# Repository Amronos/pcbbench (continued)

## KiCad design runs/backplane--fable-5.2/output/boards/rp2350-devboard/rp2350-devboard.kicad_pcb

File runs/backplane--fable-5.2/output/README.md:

# RP2350 Wi-Fi/BLE dev board (rev A)

A 76.2 x 22.86 mm, 4-layer RP2350A development board with Wi-Fi/BLE, LiPo charging with power path,
microSD, Qwiic and an addressable RGB LED. All 71 components sit on the top side so PCBWay can build it
with a single-sided SMT pass.

**Status: designed, not built.** ERC is clean; DRC is clean (0 errors, 0 unconnected, schematic parity OK,
one harmless "dangling via" warning). Nothing here has been verified on hardware — read
"What a reviewer should check" before ordering.

## Where things are

| Path | What |
|---|---|
| `boards/rp2350-devboard/` | KiCad project: `.kicad_pro`, `.kicad_sch`, `.kicad_pcb`, project symbol lib, custom DRC rule |
| `fab/rp2350-devboard-gerbers.zip` | Gerbers (RS-274X, 4 copper layers) + Excellon drill files — upload this to PCBWay |
| `fab/gerbers/` | The same files unzipped |
| `fab/assembly/rp2350-devboard-bom.csv` | BOM in PCBWay's column layout (36 lines, 71 parts, all SMD) |
| `fab/assembly/rp2350-devboard-centroid.csv` | Pick-and-place file (origin = bottom-left board corner, mm) |
| `fab/assembly/rp2350-devboard-assembly-top.pdf` | Assembly drawing with reference designators and notes |
| `fab/docs/` | Schematic PDF, fab drawing, IPC-D-356 netlist, STEP model, renders |
| `tools/` | Generator scripts. `tools/design.py` is the single source for parts, nets and placement |

The files were made with Backplane KiCad 10.99 (newer file format than stock KiCad 10.0).

## PCBWay order settings

- 4 layers, 76.2 x 22.86 mm, 1.6 mm FR-4, 1 oz outer / 0.5 oz inner is fine
- Min track/space **0.15 / 0.10 mm** (the 0.10 mm spacing occurs only where VREG_LX passes between two 0402 pads; everything else is ≥ 0.15 mm), min hole 0.3 mm, via 0.6 / 0.3 mm
- Finish: ENIG (0.4 mm pitch QFN-60), any solder-mask colour, vias tented
- Assembly: top side only, turnkey. Stencil top only
- **Not populated on purpose:** the two 1x12 2.54 mm header rows (J5, J6) and the three bottom-side SWD test pads (TP1–TP3). They are bare holes/pads and are excluded from BOM and centroid
- **L1 is polarised**: the dot on the Abracon inductor goes to pad 1 (+1V1 net, the pad towards the bottom board edge). This is in the BOM notes and on the assembly drawing

## What is on the board

| Function | Part | Notes |
|---|---|---|
| MCU | RP2350A (QFN-60, A4 stepping) | on-chip 1.1 V SMPS with the Abracon AOTA-B201610S3R3-101-T inductor, 12 MHz ABM8-272-T3 crystal |
| Flash | W25Q128JVPIQ, 16 MB | QSPI CS0 |
| PSRAM | APS6404L-3SQR-ZR, 8 MB | QSPI CS1 on GPIO0, 10 k pull-up |
| USB | USB-C (HRO TYPE-C-31-M-12) | 5.1 k CC resistors, USBLC6-2SC6 ESD, 27 Ω series resistors |
| Charger | BQ24074 | power path, ~300 mA charge, 500 mA USB input limit, orange CHG LED |
| 3.3 V | TLV75733P 1 A LDO | fed from the charger's system output; EN on a header pin |
| Battery monitor | 200 k / 200 k divider + 100 nF | VBAT/2 on GPIO29 (ADC3) |
| Wi-Fi / BLE | Raspberry Pi Radio Module 2 (CYW43439) | wired like Pico 2 W, user LED on the module's GPIO0 |
| microSD | Molex 104031-0811 | 4-bit SDIO or SPI0, card-detect on GPIO1 |
| Qwiic / STEMMA QT | JST SM04B-SRSS-TB | I2C0 on GPIO24/25 with 2.2 k pull-ups |
| RGB LED | WS2812B-2020 (V6) | GPIO23, powered from 3.3 V |
| Buttons | 2 x Omron B3U-1000P | BOOT (QSPI_SS through 1 k) and RST (RUN) |

### Pin map

| GPIO | Use | GPIO | Use |
|---|---|---|---|
| 0 | PSRAM CS (XIP_CS1) | 16 | RM2 WL_ON (also BT_ON) |
| 1 | SD card detect (low = card in) | 17 | RM2 CS |
| 2 | SD CLK (SPI0 SCK) | 18 | RM2 data (DIN direct, DOUT via 470 Ω, IRQ via 10 k) |
| 3 | SD CMD (SPI0 TX) | 19 | RM2 clock |
| 4 | SD D0 (SPI0 RX) | 20–22 | header |
| 5, 6 | SD D1, D2 | 23 | RGB LED data |
| 7 | SD D3 / CS | 24, 25 | SDA, SCL (header + Qwiic) |
| 8–15 | header | 26–28 | header (ADC0–2) |
| | | 29 | battery voltage / 2 (ADC3) |

Headers (0.8" row spacing, breadboard-friendly, pin 1 nearest the USB end):

- Top row: VBUS, VBAT, EN, GND, GP28, GP27, GP26, SCL (GP25), SDA (GP24), GP22, GP21, GP20
- Bottom row: 3V3, GND, VSYS, GND, GP8, GP9, GP10, GP11, GP12, GP13, GP14, GP15

Pin names are printed on the bottom silkscreen. SWCLK, SWDIO and GND are test pads on the bottom.

For the Pico SDK, build for a Pico 2 W-style board with `CYW43_PIN_WL_REG_ON=16`, `CYW43_PIN_WL_CS=17`,
`CYW43_PIN_WL_DATA_OUT/IN/HOST_WAKE=18`, `CYW43_PIN_WL_CLOCK=19`.

## Key decisions

- **RP2350A, not B.** 30 GPIO is enough: 14 are used on the board and 16 go to the headers.
- **Raspberry Pi RM2 for the radio** rather than an ESP32 co-processor. It works with the stock Pico SDK / MicroPython CYW43 driver, carries its own antenna and modular certification, and needs only four GPIOs. The antenna end sits at the board edge with a 5 mm copper-free strip on all layers.
- **BQ24074 + LDO.** A true power path lets the board run from USB with no battery or a flat one. I chose an LDO over a buck-boost to keep the layout simple; the cost is that 3.3 V sags once the cell drops below about 3.5 V (the RM2 wants ≥ 3.0 V, ≥ 3.2 V for full RF performance).
- **Charge current ~300 mA** (R7 = 3.0 k; I = 890 / R7). Suits cells of 300 mAh and up; change R7 for other cells.
- **Regulator layout copies the Raspberry Pi reference**: VREG_LX runs between the pads of the input and output capacitors to the inductor, with one shared capacitor for pins 53/54. That is where the 0.10 mm spacing comes from (a custom DRC rule allows it for that net only).
- **All parts on top.** This made the board long (76 mm). Putting the microSD socket on the back would save about 14 mm at the price of double-sided assembly.
- **How the files were made.** Schematic and board are generated from `tools/design.py`. The RP2350 fan-out, regulator, QSPI, SD bus and other critical routes are explicit coordinates in that file; the remaining ~60 connections were finished by a small grid router (`tools/maze.py`) and checked with KiCad's DRC. The routing is electrically clean but not hand-polished.

## What a reviewer should check

1. **Battery polarity.** J2 pin 2 (marked `+`, the pad nearer the bottom edge) is positive. I could not confirm this matches the common Adafruit/SparkFun JST-PH wiring. Check your cell before plugging in — there is no reverse-polarity protection.
2. **microSD card-detect pins.** I wired socket pad 9 to GPIO1 and pad 10 to GND, assuming the switch sits between those two pads. If Molex's drawing says otherwise, card detect will read wrong; the card itself still works.
3. **RM2 footprint** is KiCad's library footprint `RF_Module:RMC20452T`; I checked its pad positions against the RM2 datasheet drawing, not against a physical module.
4. **Three signals use short tracks on In2** (the 3.3 V plane): QSPI SD1 and SD2 to the PSRAM, PSRAM CS, and RUN to the reset button. They were the only way to cross the SD bus and radio lines with single-sided assembly. They cut narrow slots in the plane; the GND plane on In1 is unbroken.
5. **Decoupling is a compromise.** Most mid-side RP2350 supply pins drop to the planes through vias inside the pad ring, with their 100 nF capacitors 3–6 mm away. Raspberry Pi's own minimal design makes a similar trade, but this is the first thing I would probe on a prototype (1.1 V ripple under Wi-Fi load).
6. **Things left out to keep the layout routable:**
   - no external pull-ups on the SD lines (use the RP2350's internal ones);
   - no external pull-up on RUN (internal only) and RUN is not on a header pin;
   - the RM2's GPIO2 is not wired to VBUS sense as on a Pico W;
   - no fiducials or mounting holes.
7. **Battery sense leakage.** The divider draws about 10 µA from the cell all the time, and GPIO29 is not fail-safe: with 3.3 V switched off through EN a few µA flow into the pin.
8. **Power track widths** are 0.25–0.4 mm for VBUS/VBAT/VSYS. That is adequate for the 500 mA input limit but not generous.
9. **BOM part numbers.** ICs, connectors, LEDs and switches were checked against LCSC stock on 2026-11-09 (the RM2 had only 51 pieces there; PCBWay may source it elsewhere). The Yageo/Samsung passive part numbers were written from the manufacturers' naming scheme and not looked up — any equivalent 0402/0603 part of the same value and rating is fine.
10. The USB pair is routed for full-speed only (no impedance control), which is all the RP2350 supports.

## Regenerating

```
tools/build_all.sh            # schematic, netlist check, pours, DRC, fab outputs (keeps the routing)
tools/build_all.sh --reroute  # also throws the routing away and routes again (about 2 minutes)
```

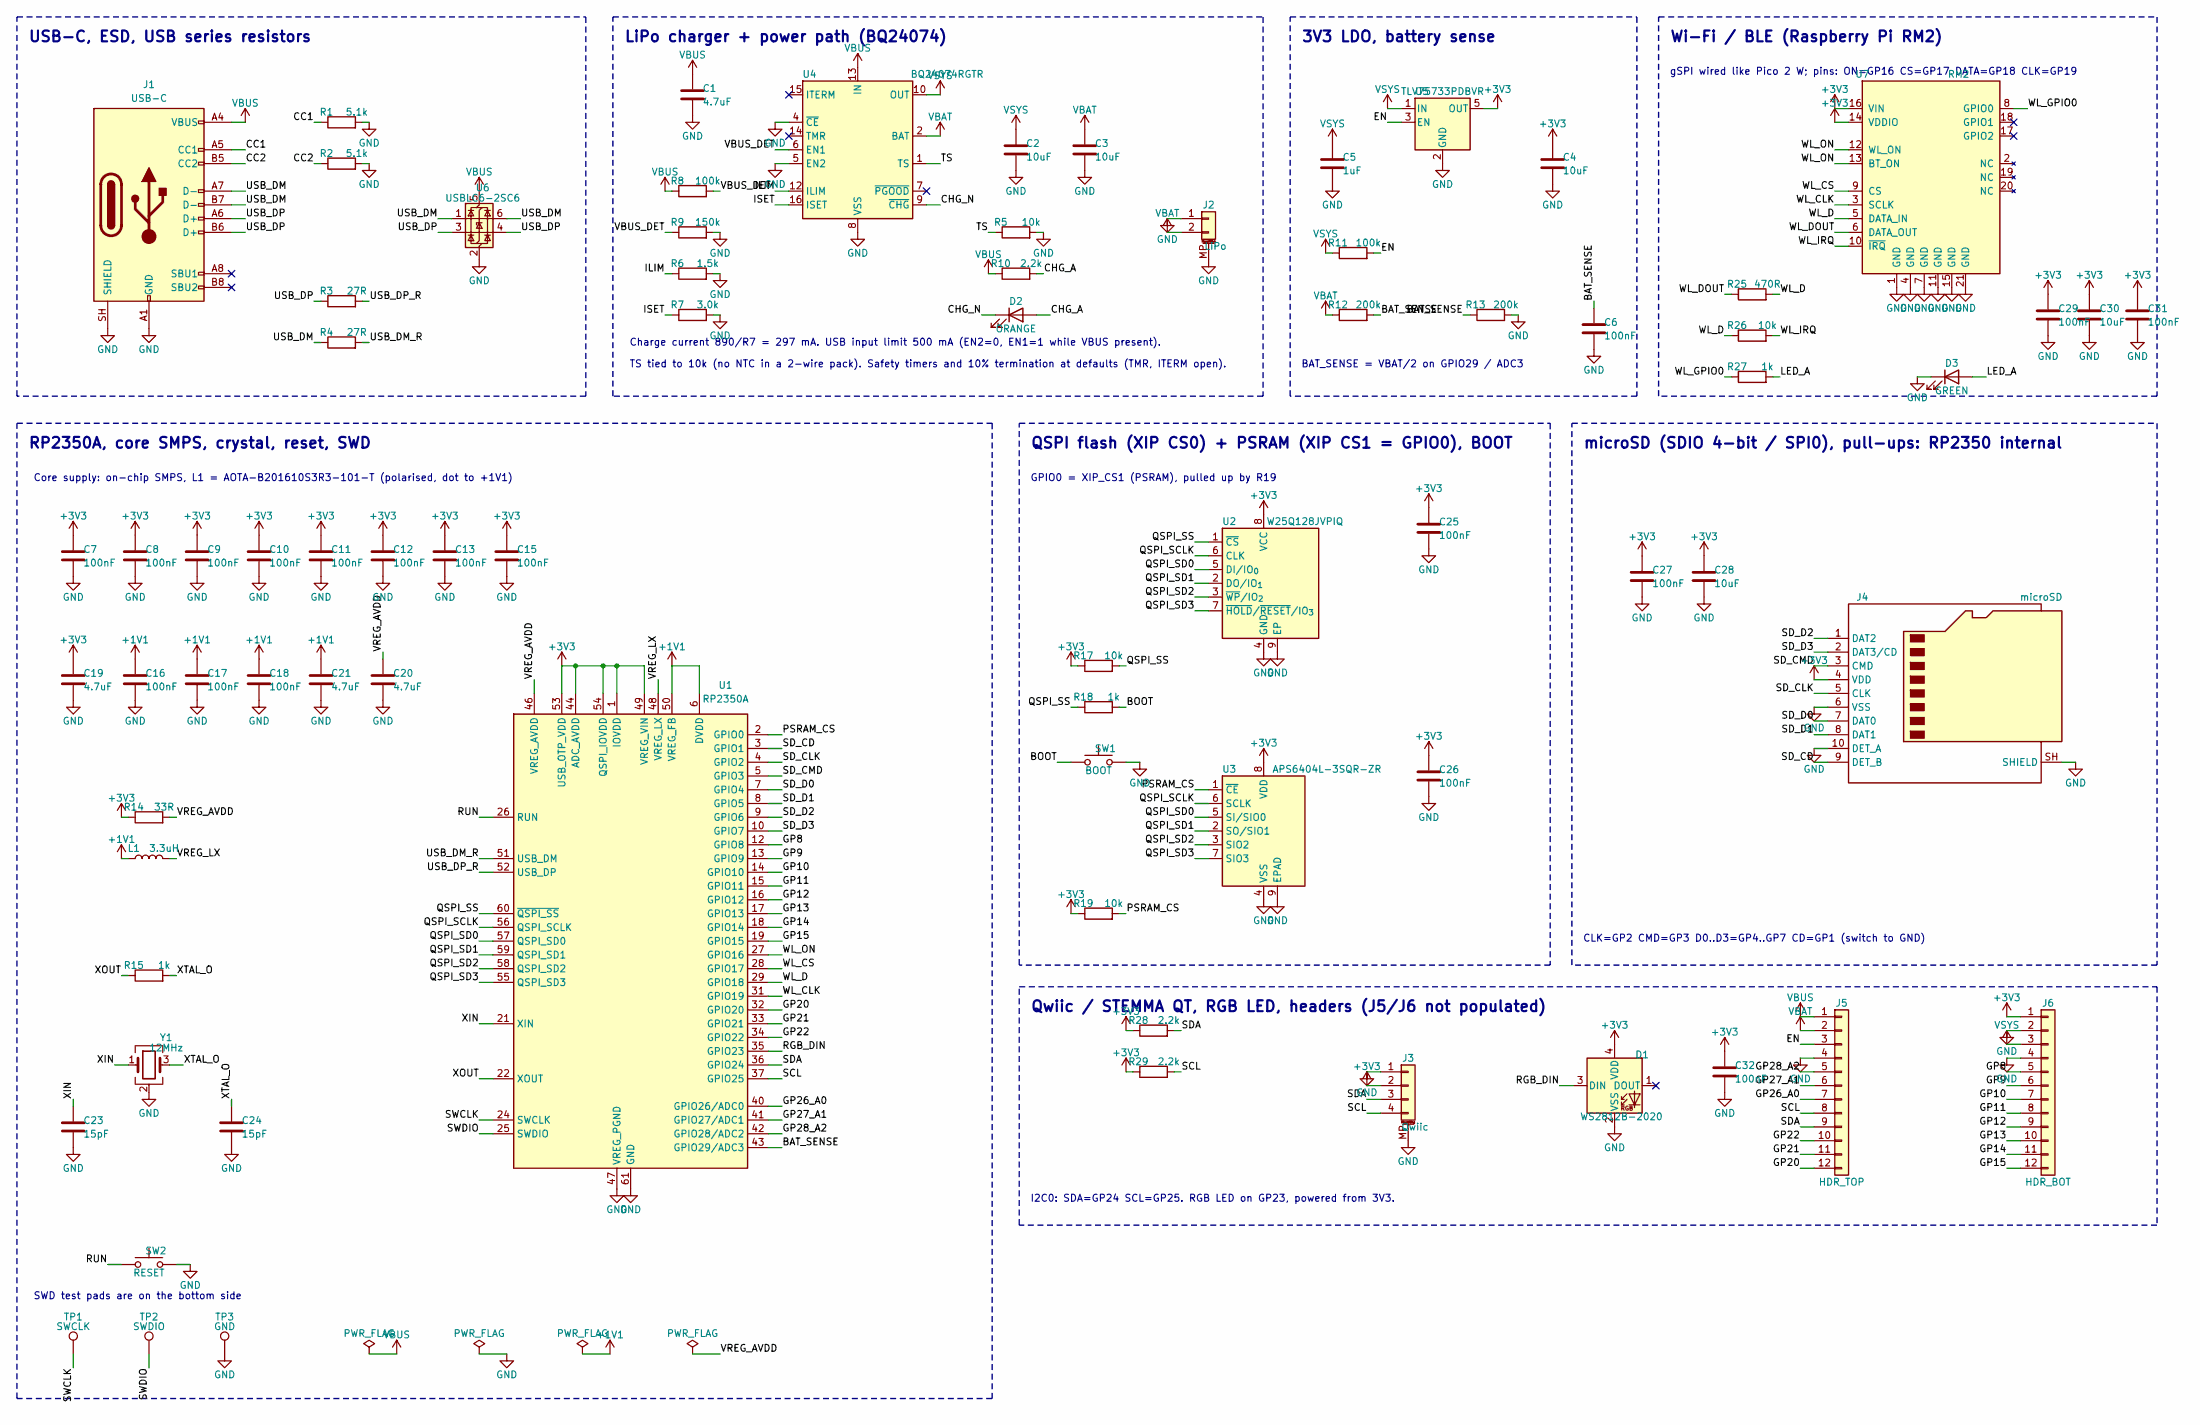
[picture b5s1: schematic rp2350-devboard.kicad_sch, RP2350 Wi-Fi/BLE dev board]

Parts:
C1: 4.7uF; C_0603_1608Metric; MPN CL10A475KA8NQNC
C2, C3, C4, C28, C30: 10uF; C_0603_1608Metric; MPN CL10A106MA8NRNC
C5: 1uF; C_0402_1005Metric; MPN CL05A105KA5NQNC
C6, C7, C8, C9, C10, C11, C12, C13, C15, C16, C17, C18, C25, C26, C27, C29, C31, C32: 100nF; C_0402_1005Metric; MPN CL05B104KO5NNNC
C19, C20, C21: 4.7uF; C_0402_1005Metric; MPN CL05A475MP5NRNC
C23, C24: 15pF; C_0402_1005Metric; MPN CL05C150JB5NNNC
D1: WS2812B-2020; LED_WS2812B-2020_PLCC4_2.0x2.0mm; MPN WS2812B-2020; LCSC C52917434
D2: ORANGE; LED_0603_1608Metric; MPN XL-1608UOC-06; LCSC C965800
D3: GREEN; LED_0603_1608Metric; MPN XL-1608SYGC-06; LCSC C965805
J1: USB-C; USB_C_Receptacle_HRO_TYPE-C-31-M-12; MPN TYPE-C-31-M-12; LCSC C165948
J2: LiPo; JST_PH_S2B-PH-SM4-TB_1x02-1MP_P2.00mm_Horizontal; MPN S2B-PH-SM4-TB(LF)(SN); LCSC C295747
J3: Qwiic; JST_SH_SM04B-SRSS-TB_1x04-1MP_P1.00mm_Horizontal; MPN SM04B-SRSS-TB(LF)(SN); LCSC C160404
J4: microSD; microSD_HC_Molex_104031-0811; MPN 104031-0811; LCSC C585350
J5: HDR_TOP; PinHeader_1x12_P2.54mm_Vertical
J6: HDR_BOT; PinHeader_1x12_P2.54mm_Vertical
L1: 3.3uH; L_Murata_DFE201610P; MPN AOTA-B201610S3R3-101-T; LCSC C42411119
R1, R2: 5.1k; R_0402_1005Metric; MPN RC0402FR-075K1L
R3, R4: 27R; R_0402_1005Metric; MPN RC0402FR-0727RL
R5, R17, R19, R26: 10k; R_0402_1005Metric; MPN RC0402FR-0710KL
R6: 1.5k; R_0402_1005Metric; MPN RC0402FR-071K5L
R7: 3.0k; R_0402_1005Metric; MPN RC0402FR-073KL
R8, R11: 100k; R_0402_1005Metric; MPN RC0402FR-07100KL
R9: 150k; R_0402_1005Metric; MPN RC0402FR-07150KL
R10, R28, R29: 2.2k; R_0402_1005Metric; MPN RC0402FR-072K2L
R12, R13: 200k; R_0402_1005Metric; MPN RC0402FR-07200KL
R14: 33R; R_0402_1005Metric; MPN RC0402FR-0733RL
R15, R18, R27: 1k; R_0402_1005Metric; MPN RC0402FR-071KL
R25: 470R; R_0402_1005Metric; MPN RC0402FR-07470RL
SW1: BOOT; SW_SPST_B3U-1000P; MPN B3U-1000P; LCSC C231329
SW2: RESET; SW_SPST_B3U-1000P; MPN B3U-1000P; LCSC C231329
TP1: SWCLK; TestPoint_Pad_D1.0mm
TP2: SWDIO; TestPoint_Pad_D1.0mm
TP3: GND; TestPoint_Pad_D1.5mm
U1: RP2350A; QFN-60-1EP_7x7mm_P0.4mm_EP3.4x3.4mm; MPN RP2350A0A4; LCSC C42411118
U2: W25Q128JVPIQ; WSON-8-1EP_6x5mm_P1.27mm_EP3.4x4.3mm; MPN W25Q128JVPIQ; LCSC C190862
U3: APS6404L-3SQR-ZR; Winbond_USON-8-1EP_3x2mm_P0.5mm_EP0.2x1.6mm; MPN APS6404L-3SQR-ZR; LCSC C3040877
U4: BQ24074RGTR; VQFN-16-1EP_3x3mm_P0.5mm_EP1.6x1.6mm; MPN BQ24074RGTR; LCSC C54313
U5: TLV75733PDBVR; SOT-23-5; MPN TLV75733PDBVR; LCSC C485517
U6: USBLC6-2SC6; SOT-23-6; MPN USBLC6-2SC6; LCSC C7519
U7: RM2; RMC20452T; MPN RMC20452T; LCSC C49451547
Y1: 12MHz; Crystal_SMD_3225-4Pin_3.2x2.5mm; MPN ABM8-272-T3; LCSC C20625731

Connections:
+1V1: C16.1, C17.1, C18.1, C21.1, L1.1, U1.6 (DVDD), U1.23 (DVDD), U1.39 (DVDD), U1.50 (VREG_FB)
+3V3: C4.1, C7.1, C8.1, C9.1, C10.1, C11.1, C12.1, C13.1, C15.1, C19.1, C25.1, C26.1, C27.1, C28.1, C29.1, C30.1, C31.1, C32.1, D1.4 (VDD), J3.2, J4.4 (VDD), J6.1, R14.1, R17.1, R19.1, R28.1, R29.1, U1.1 (IOVDD), U1.11 (IOVDD), U1.20 (IOVDD), U1.30 (IOVDD), U1.38 (IOVDD), U1.44 (ADC_AVDD), U1.45 (IOVDD), U1.49 (VREG_VIN), U1.53 (USB_OTP_VDD), U1.54 (QSPI_IOVDD), U2.8 (VCC), U3.8 (VDD), U5.5 (OUT), U7.14 (VDDIO), U7.16 (VIN)
/BAT_SENSE: C6.1, R12.2, R13.1, U1.43 (GPIO29/ADC3)
/BOOT: R18.2, SW1.1
/CC1: J1.A5 (CC1), R1.1
/CC2: J1.B5 (CC2), R2.1
/CHG_A: D2.2 (A), R10.2
/CHG_N: D2.1 (K), U4.9 (~CHG)
/EN: J5.3, R11.2, U5.3 (EN)
/GP8: J6.5, U1.12 (GPIO8)
/GP9: J6.6, U1.13 (GPIO9)
/GP10: J6.7, U1.14 (GPIO10)
/GP11: J6.8, U1.15 (GPIO11)
/GP12: J6.9, U1.16 (GPIO12)
/GP13: J6.10, U1.17 (GPIO13)
/GP14: J6.11, U1.18 (GPIO14)
/GP15: J6.12, U1.19 (GPIO15)
/GP20: J5.12, U1.32 (GPIO20)
/GP21: J5.11, U1.33 (GPIO21)
/GP22: J5.10, U1.34 (GPIO22)
/GP26_A0: J5.7, U1.40 (GPIO26/ADC0)
/GP27_A1: J5.6, U1.41 (GPIO27/ADC1)
/GP28_A2: J5.5, U1.42 (GPIO28/ADC2)
/ILIM: R6.1, U4.12 (ILIM)
/ISET: R7.1, U4.16 (ISET)
/LED_A: D3.2 (A), R27.2
/PSRAM_CS: R19.2, U1.2 (GPIO0), U3.1 (~CE)
/QSPI_SCLK: U1.56 (QSPI_SCLK), U2.6 (CLK), U3.6 (SCLK)
/QSPI_SD0: U1.57 (QSPI_SD0), U2.5 (DI/IO_{0}), U3.5 (SI/SIO0)
/QSPI_SD1: U1.59 (QSPI_SD1), U2.2 (DO/IO_{1}), U3.2 (SO/SIO1)
/QSPI_SD2: U1.58 (QSPI_SD2), U2.3 (~WP/IO_{2}), U3.3 (SIO2)
/QSPI_SD3: U1.55 (QSPI_SD3), U2.7 (~HOLD/~RESET/IO_{3}), U3.7 (SIO3)
/QSPI_SS: R17.2, R18.1, U1.60 (~QSPI_SS), U2.1 (~CS)
/RGB_DIN: D1.3 (DIN), U1.35 (GPIO23)
/RUN: SW2.1, U1.26 (RUN)
/SCL: J3.4, J5.8, R29.2, U1.37 (GPIO25)
/SDA: J3.3, J5.9, R28.2, U1.36 (GPIO24)
/SD_CD: J4.9 (DET_B), U1.3 (GPIO1)
/SD_CLK: J4.5 (CLK), U1.4 (GPIO2)
/SD_CMD: J4.3 (CMD), U1.5 (GPIO3)
/SD_D0: J4.7 (DAT0), U1.7 (GPIO4)
/SD_D1: J4.8 (DAT1), U1.8 (GPIO5)
/SD_D2: J4.1 (DAT2), U1.9 (GPIO6)
/SD_D3: J4.2 (DAT3/CD), U1.10 (GPIO7)
/SWCLK: TP1.1, U1.24 (SWCLK)
/SWDIO: TP2.1, U1.25 (SWDIO)
/TS: R5.1, U4.1 (TS)
/USB_DM: J1.A7 (D-), J1.B7 (D-), R4.1, U6.1 (I/O1), U6.6 (I/O1)
/USB_DM_R: R4.2, U1.51 (USB_DM)
/USB_DP: J1.A6 (D+), J1.B6 (D+), R3.1, U6.3 (I/O2), U6.4 (I/O2)
/USB_DP_R: R3.2, U1.52 (USB_DP)
/VBUS_DET: R8.2, R9.1, U4.6 (EN1)
/VREG_AVDD: C20.1, R14.2, U1.46 (VREG_AVDD)
/VREG_LX: L1.2, U1.48 (VREG_LX)
/WL_CLK: U1.31 (GPIO19), U7.3 (SCLK)
/WL_CS: U1.28 (GPIO17), U7.9 (CS)
/WL_D: R25.2, R26.1, U1.29 (GPIO18), U7.5 (DATA_IN)
/WL_DOUT: R25.1, U7.6 (DATA_OUT)
/WL_GPIO0: R27.1, U7.8 (GPIO0)
/WL_IRQ: R26.2, U7.10 (~IRQ)
/WL_ON: U1.27 (GPIO16), U7.12 (WL_ON), U7.13 (BT_ON)
/XIN: C23.1, U1.21 (XIN), Y1.1
/XOUT: R15.1, U1.22 (XOUT)
/XTAL_O: C24.1, R15.2, Y1.3
GND: C1.2, C2.2, C3.2, C4.2, C5.2, C6.2, C7.2, C8.2, C9.2, C10.2, C11.2, C12.2, C13.2, C15.2, C16.2, C17.2, C18.2, C19.2, C20.2, C21.2, C23.2, C24.2, C25.2, C26.2, C27.2, C28.2, C29.2, C30.2, C31.2, C32.2, D1.2 (VSS), D3.1 (K), J1.A1 (GND), J1.A12 (GND), J1.B1 (GND), J1.B12 (GND), J1.SH (SHIELD), J2.1, J2.MP (MountPin), J3.1, J3.MP (MountPin), J4.6 (VSS), J4.10 (DET_A), J4.SH (SHIELD), J5.4, J6.2, J6.4, R1.2, R2.2, R5.2, R6.2, R7.2, R9.2, R13.2, SW1.2, SW2.2, TP3.1, U1.47 (VREG_PGND), U1.61 (GND), U2.4 (GND), U2.9 (EP), U3.4 (VSS), U3.9 (EPAD), U4.4 (~CE), U4.5 (EN2), U4.8 (VSS), U4.17 (VSS), U5.2 (GND), U6.2 (GND), U7.1 (GND), U7.4 (GND), U7.7 (GND), U7.11 (GND), U7.15 (GND), U7.21 (GND), Y1.2 (G), Y1.4 (G)
VBAT: C3.1, J2.2, J5.2, R12.1, U4.2 (BAT), U4.3 (BAT)
VBUS: C1.1, J1.A4 (VBUS), J1.A9 (VBUS), J1.B4 (VBUS), J1.B9 (VBUS), J5.1, R8.1, R10.1, U4.13 (IN), U6.5 (VBUS)
VSYS: C2.1, C5.1, J6.3, R11.1, U4.10 (OUT), U4.11 (OUT), U5.1 (IN)

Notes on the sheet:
USB-C, ESD, USB series resistors
LiPo charger + power path (BQ24074)
3V3 LDO, battery sense
Wi-Fi / BLE (Raspberry Pi RM2)
RP2350A, core SMPS, crystal, reset, SWD
QSPI flash (XIP CS0) + PSRAM (XIP CS1 = GPIO0), BOOT
microSD (SDIO 4-bit / SPI0), pull-ups: RP2350 internal
Qwiic / STEMMA QT, RGB LED, headers (J5/J6 not populated)
Charge current 890/R7 = 297 mA. USB input limit 500 mA (EN2=0, EN1=1 while VBUS present).
TS tied to 10k (no NTC in a 2-wire pack). Safety timers and 10% termination at defaults (TMR, ITERM open).
BAT_SENSE = VBAT/2 on GPIO29 / ADC3
gSPI wired like Pico 2 W; pins: ON=GP16 CS=GP17 DATA=GP18 CLK=GP19
SWD test pads are on the bottom side
Core supply: on-chip SMPS, L1 = AOTA-B201610S3R3-101-T (polarised, dot to +1V1)
GPIO0 = XIP_CS1 (PSRAM), pulled up by R19
CLK=GP2 CMD=GP3 D0..D3=GP4..GP7 CD=GP1 (switch to GND)
I2C0: SDA=GP24 SCL=GP25. RGB LED on GP23, powered from 3V3.

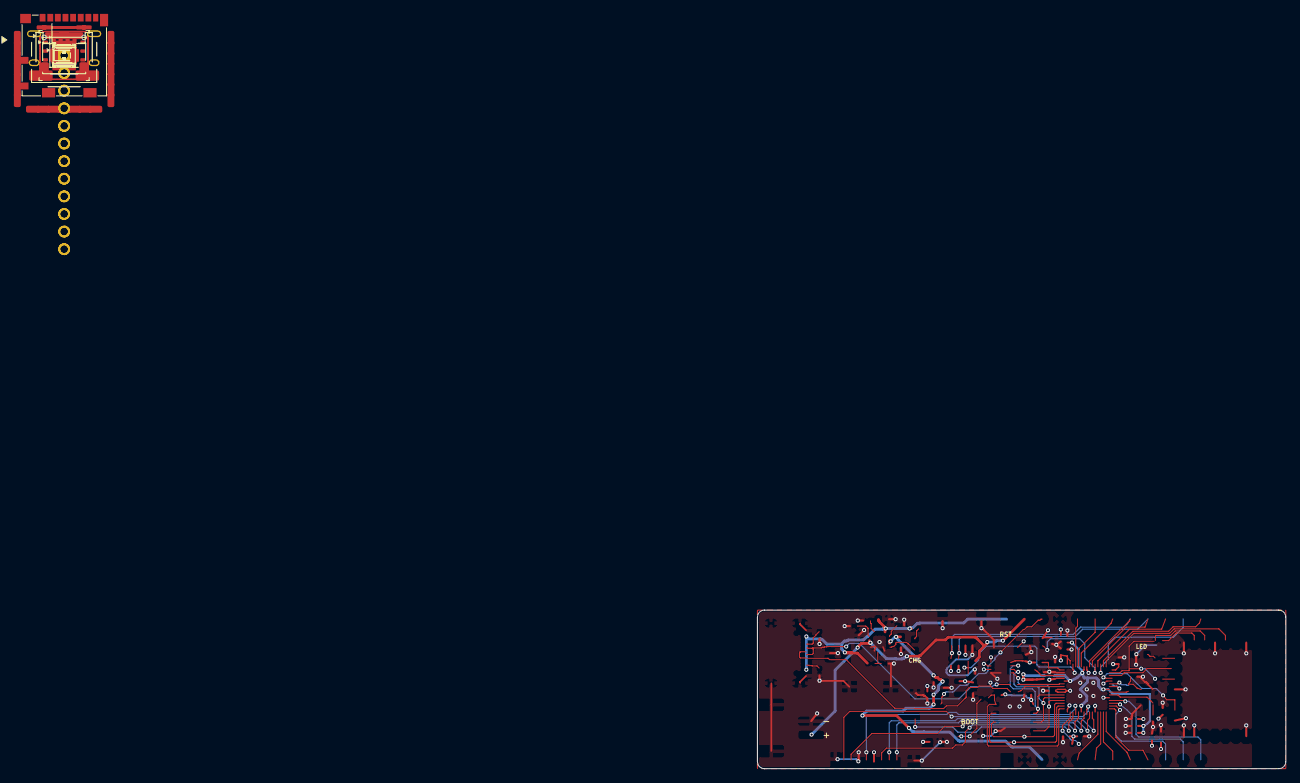
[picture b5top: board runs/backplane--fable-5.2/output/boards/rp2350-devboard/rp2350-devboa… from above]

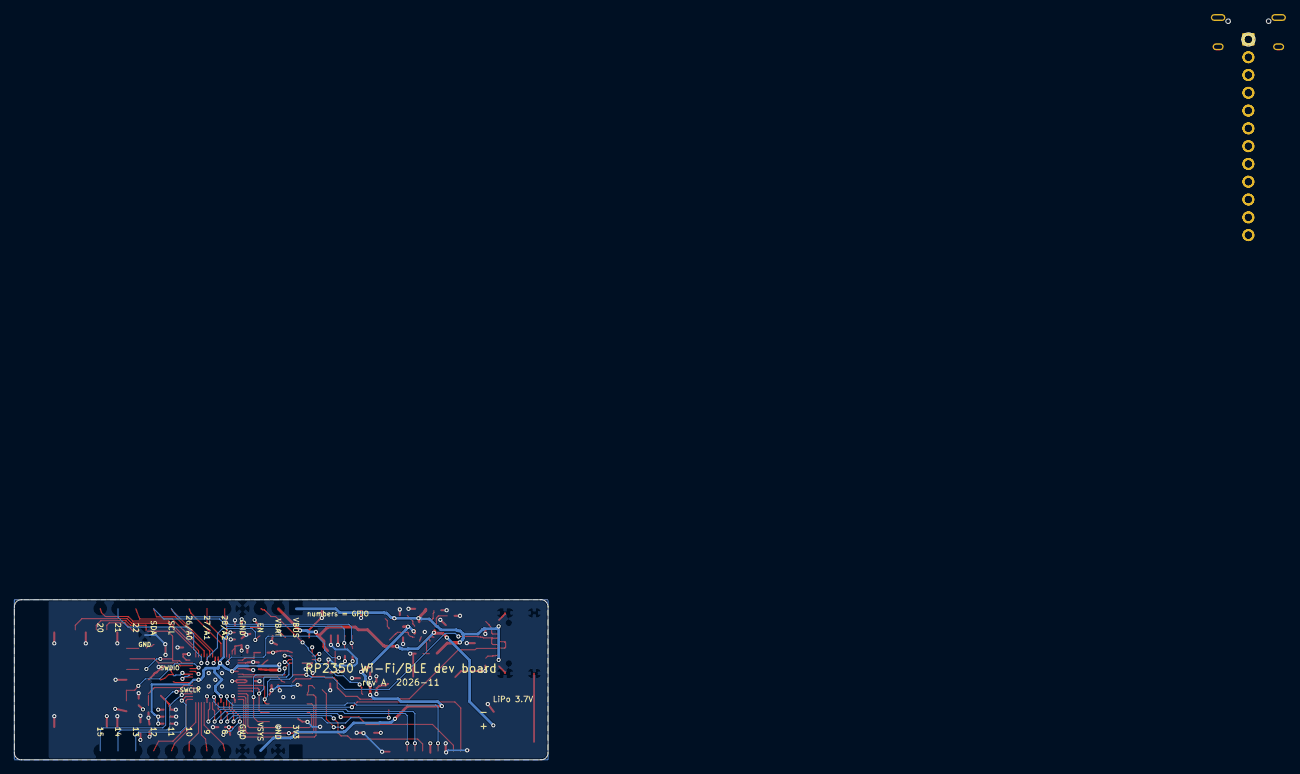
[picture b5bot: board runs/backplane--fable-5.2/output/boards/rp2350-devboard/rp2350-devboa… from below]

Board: 4 copper layers, 76.2 x 22.9 mm, 76 parts (3 on the bottom side), 68 nets.

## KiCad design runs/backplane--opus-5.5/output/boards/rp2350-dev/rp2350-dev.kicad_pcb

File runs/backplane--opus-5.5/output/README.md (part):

# RP2350 Wireless Dev Board (Rev A)

An 80 × 38 mm, 4-layer RP2350 development board designed for **turnkey manufacture and assembly
by PCBWay** (every part on the BOM is placed by PCBWay; all SMD parts are on the top side, the two
pin headers are the only through-hole parts).

| Feature | Implementation |
|---|---|
| MCU | Raspberry Pi **RP2350A** (QFN-60), 150 MHz dual Cortex-M33 / Hazard3 |
| Flash | **W25Q128JVSIQ**, 16 MB QSPI on `QSPI_SS` |
| PSRAM | **APS6404L-3SQR-SN**, 8 MB QSPI PSRAM on XIP_CS1 = **GPIO8** |
| USB | **USB-C** (GCT USB4105-GF-A), USB 2.0 FS device + 5 V input, 5.1 kΩ Rd on CC1/CC2, USBLC6-2SC6 ESD |
| Battery | 1-cell Li-Po on **JST-PH 2-pin** (pin 1 = GND, pin 2 = +) |
| Charger / power-path | **TI BQ24074** (DPPM power-path: USB powers the system and charges the cell, the cell takes over seamlessly) |
| Battery monitor | VBAT / 3 divider on **GPIO29 / ADC3** (same scaling as Pico 2), charger `~CHG` on GPIO7, `~PGOOD` (USB present) on GPIO6 |
| 3.3 V | **TLV75733P** 1 A LDO from VSYS, enable on header (`EN`) |
| Wi-Fi + Bluetooth LE | **ESP32-C6-MINI-1-N4** module (Wi-Fi 6 2.4 GHz, BLE 5, 802.15.4), PCB antenna at the board edge, UART link with RTS/CTS to RP2350 |
| microSD | **Hirose DM3AT-SF-PEJM5** push-push socket with card detect, wired for 4-bit SDIO (PIO) and SPI |
| Qwiic / STEMMA QT | JST-SH 4-pin (SM04B-SRSS-TB), I²C0 on GPIO16/17, 4.7 kΩ pull-ups, 3.3 V |
| RGB LED | **WS2812B-2020** addressable LED on GPIO24 |
| Other | BOOT and RESET buttons, user LED (GPIO25), charge LED, SWD on JST-SH 3-pin (Raspberry Pi Debug Probe pinout), 2 × 12-pin 2.54 mm headers |

## Repository layout

```
boards/rp2350-dev/      KiCad 10 project (schematic: 5 sheets, 4-layer PCB, project footprint library)
  rp2350-dev.kicad_pro / .kicad_sch / .kicad_pcb
  power.kicad_sch mcu.kicad_sch wireless.kicad_sch io.kicad_sch
  lib/RP2350_Dev.pretty  project footprints (see "Footprints")
fab/                    everything PCBWay needs (see "Ordering from PCBWay")
scripts/                the generators used to build the design (design.py is the single source of truth)
third_party/            Raspberry Pi RP2350A minimal design (MIT) used as the core reference
```

## Footprints

Standard KiCad library footprints are used except for `boards/rp2350-dev/lib/RP2350_Dev.pretty`:

| Footprint | Source |
|---|---|
| `RP2350A_QFN60_RPi` | RPi reference RP2350A footprint, with its 9 EP vias and embedded 3D model |
| `L_Abracon_AOTA-B201610` | RPi reference footprint for the polarity-marked 3.3 µH inductor |
| `C_0402_RPi`, `C_0402_RPi_Wide`, `R_0402_RPi`, `Crystal_3225_RPi`, `SOIC-8_5.3mm_RPi` | RPi reference passive/crystal/flash footprints (keep the copied tracks landing exactly on the pads) |
| `ESP32-C6-MINI-1_BoardEdge` | KiCad `RF_Module:ESP32-C6-MINI-1` with the courtyard cut to the module outline and an all-layer copper keepout under the antenna. The stock footprint draws Espressif's ideal 43 mm-wide antenna clearance as its courtyard. |

`scripts/extract_rpi.py` and `scripts/make_esp_fp.py` regenerate them.

## GPIO map

| GPIO | Function | GPIO | Function |
|---|---|---|---|
| 0 | UART0 TX (header J7) | 16 | I²C0 SDA (Qwiic + header) |
| 1 | UART0 RX (header J7) | 17 | I²C0 SCL (Qwiic + header) |
| 2–5 | header J7 | 18 | ESP32-C6 `EN` (drive low = reset; use open-drain style) |
| 6 | BQ24074 `~PGOOD` (low = USB power present) | 19 | ESP32-C6 `IO9` boot strap (low at reset = ROM download) |
| 7 | BQ24074 `~CHG` (low = charging) | 20 | UART1 TX → ESP RXD0 |
| 8 | PSRAM CS (XIP_CS1) | 21 | UART1 RX ← ESP TXD0 |
| 9 | microSD card detect (switch to GND, 10 k pull-up) | 22 | UART1 CTS ← ESP IO6 (RTS) |
| 10 | SD CLK (SPI1 SCK) | 23 | UART1 RTS → ESP IO7 (CTS) |
| 11 | SD CMD (SPI1 MOSI) | 24 | WS2812B data |
| 12–15 | SD DAT0–DAT3 (DAT0 = SPI1 MISO, DAT3 = CS) | 25 | user LED (yellow) |
| | | 26–28 | ADC0–2 (header J6) |
| | | 29 | VBAT / 3 (ADC3) |

Headers (pin 1 at the left, looking at the top side):

* **J6** (top edge): VBUS, VSYS, VBAT, GND, 3V3, EN, RUN, GND, A0/GP26, A1/GP27, A2/GP28, GND
* **J7** (bottom edge): GP0/TX, GP1/RX, GP2, GP3, GP4, GP5, GND, SDA/GP16, SCL/GP17, 3V3, GND, GND

## Key design decisions

1. **RP2350 core copied from the Raspberry Pi reference.** Raspberry Pi say the RP2350 switching
   regulator layout must be copied exactly ("if you choose not to use our example, then you do so at
   your own risk"). The RP2350A Minimal design R4 (MIT licence, in `third_party/`) was used verbatim
   for the RP2350A, its footprint with EP vias, the 3.3 µH polarity-marked Abracon
   AOTA-B201610S3R3-101-T inductor, VREG_VIN/VREG_LX/VREG_AVDD capacitors and 33 Ω filter, all
   decoupling capacitors, the 12 MHz ABM8-272-T3 crystal (15 pF, 1 kΩ), USB 27 Ω resistors and the
   QSPI flash with its CS pull-up, 0 Ω link and BOOTSEL resistor. `scripts/gen_pcb.py` places those
   parts at the reference positions (rotated 90°) and copies the reference copper — tracks, vias and the
   VREG_LX / +1V1 / +3V3 / PGND copper areas — for the power, regulator, crystal and USB nets. The QSPI
   bus was not copied. The reference has only the flash, so the bus was re-routed to reach the PSRAM too.
   Everything else was placed for this board and routed as described below.
2. **PSRAM on GPIO8**, not GPIO0: GPIO8 is a valid XIP_CS1 pin and matches the Adafruit Feather
   RP2350, so existing board configurations work (`PICO_RP2350_PSRAM_CS=8`). It also keeps GPIO0/1 free
   for the SDK's default UART0.
3. **ESP32-C6-MINI-1 for Wi-Fi/BLE.** The pre-certified module avoids RF matching work and is easy for
   PCBWay to source. It runs Espressif's ESP-AT or ESP-Hosted firmware as a co-processor on UART1 with
   hardware flow control. The RP2350 drives the module's `EN` and `IO9` strap, so it can put the ESP into ROM
   download mode and re-flash it over the same UART (esp-serial-flasher). `IO8` is pulled up, as needed for
   download mode. The ESP's native USB (IO12/IO13) goes to test pads TP1/TP2 for factory programming.
   **The ESP32-C6 is supplied blank**: flash ESP-AT (configured for UART0 TX=IO16 / RX=IO17, RTS=IO6,
   CTS=IO7) or ESP-Hosted before use, either from the RP2350 or through the USB test pads TP1/TP2.
   PCBWay also offers pre-programming as a paid option.
   The antenna sits at the right board edge. A keepout on all copper layers covers the antenna and the
   strip to the edge. There is no copper under or beside the antenna.
4. **BQ24074 charger with real power-path.** It was chosen over an MCP73831 + MOSFET load share for proper DPPM,
   input OVP to 10.5 V (28 V tolerant), a 1.5 A capability and status pins. Configuration: EN2 = 1,
   EN1 = 0 → input current limit set by R4 = 1.5 kΩ (≈1.03 A); R5 = 2 kΩ → 445 mA fast-charge
   (good for ≥ 450 mAh cells; change R5 for other cells: I = 890 / R); TMR open = default safety timers;
   ITERM open = 10 % termination; TS tied to 10 kΩ (most hobby cells have no NTC; fit an NTC pack and
   remove R3 if you want temperature qualification). On USB, VSYS is regulated to 4.4 V. On battery,
   VSYS = VBAT.
5. **LDO rather than buck-boost** for 3.3 V: the TLV75733P (1 A, low dropout) covers ESP32-C6 TX
   peaks (≈350 mA) plus RP2350, SD and LED. Dissipation at 4.4 V in is ≤ 0.35 W at 300 mA. On
   battery, 3V3 stays regulated down to VBAT ≈ 3.5 V and then tracks the battery (≈ 3.3 V at 3.5 V cell).
6. **Battery monitor**: a 200 k / 100 k divider (≈14 µA load on the cell, 100 nF filter) gives VBAT/3 on
   ADC3 — identical to the Pico 2's VSYS/3 so existing code works (`v = raw * 3.3 / 4096 * 3`).
7. **4-layer stack-up** (PCBWay standard 1.6 mm): F.Cu signals + GND pour / In1 solid GND / In2 solid
   3.3 V / B.Cu signals + GND pour. This gives every IC a low-impedance return path. The USB pair
   runs over solid ground.
8. **microSD wiring** supports both modes: D0–D3 sit on consecutive GPIO12–15 for PIO SDIO
   (e.g. `no-OS-FatFS-SD-SDIO-SPI-RPi-Pico`), and CLK/CMD/D0/D3 line up with SPI1 for SPI mode.
9. **Assembly constraints**: all SMD parts are on the top (single-sided reflow). The two headers are THT,
   fitted from the bottom (plastic spacer under the board, so the board plugs straight into a
   breadboard) and hand/selective soldered. Fiducials: 3 on top. The board text includes `WayWayWay`
   (bottom side), where PCBWay prints its order number.

## Reproducing / tools

* KiCad 10.99 (Backplane build of KiCad master). The files use the current master format; to open them in
  stock KiCad 10.0, export a copy with `kicad-cli project downgrade --target 10.0`.
* Python 3 scripts in `scripts/` (the s-expression reader/writer is self-contained; `fab.py` and
  `render.py` also need `openpyxl`, `numpy` and `pillow`).
* `gen_sch.py` → schematic, `gen_pro.py` → project/design rules, `build.py finish` → PCB + zone fill +
  DRC, `fab.py` → everything in `fab/`.
* Freerouting 1.9.0 (Java 21, run under Xvfb) for autorouting, through `dsn.py`, which exports
  Specctra DSN and imports SES.

## Ordering from PCBWay

Upload `fab/rp2350-dev-gerbers.zip` for the PCB and `fab/rp2350-dev-BOM-pcbway.xlsx` +
`fab/rp2350-dev-CPL-pcbway.csv` for assembly. Suggested PCB options:

| Option | Value |
|---|---|
| Layers | 4 (F.Cu / In1 GND / In2 3V3 / B.Cu) |
| Size | 80 × 38 mm, 1 design |
| Material / thickness | FR-4 TG150, 1.6 mm |
| Stack-up | standard PCBWay 4-layer (prepreg ≈ 0.21 mm, core ≈ 1.07 mm), see `fab/stackup.csv` |
| Copper | 1 oz outer, 0.5 oz inner |
| Min track / space | 0.15 mm / 0.15 mm (6/6 mil) |
| Min hole | 0.25 mm (RP2350 EP / core vias from the RPi reference); routing vias 0.3 mm / 0.6 mm pad |
| Surface finish | ENIG (recommended for the 0.4 mm-pitch QFN and the 1.6 mm-pitch ESP32 LGA) |
| Solder mask / silk | green / white, vias tented |
| Assembly | Turnkey, top side SMD (one side), 2 THT headers (bottom-side insertion) |

Contents of `fab/`:

| File | Purpose |
|---|---|
| `rp2350-dev-gerbers.zip` | Gerber X2 for all 4 copper layers, masks, paste, silk, outline + Excellon drills (PTH/NPTH) + drill map |
| `gerbers/` | the same files unzipped |
| `rp2350-dev-BOM-pcbway.xlsx` / `.csv` | PCBWay BOM template: designators, qty, manufacturer, MPN, description, package, SMD/THT, side, LCSC #, notes |
| `rp2350-dev-CPL-pcbway.csv` | centroid / pick-and-place file: mm, origin at the board's bottom-left corner (Y up), the same origin as the Gerbers and drill files |
| `rp2350-dev-pos-kicad.csv` | raw KiCad position file |
| `rp2350-dev-assembly-top.pdf` / `-bottom.pdf` | assembly drawings with reference designators (silkscreen refs are hidden on this dense board) |
| `rp2350-dev-schematic.pdf` | schematic |
| `rp2350-dev-ipc356.d356` | IPC-D-356 netlist for flying-probe electrical test |
| `rp2350-dev.step` | 3D model |
| `stackup.csv`, `drc-report.txt`, `erc-report.txt` | stack-up and the final DRC/ERC reports |
| `renders/` | top/bottom renders |

### Notes for PCBWay engineering / assembly

* **L1 (AOTA-B201610S3R3-101-T) is polarity-marked** and its orientation matters for the RP2350
  regulator. Place the dot at pin 1 as in the footprint/assembly drawing. The parts come aligned on the reel.
* The **RP2350A EP** has 9 vias in the pad (0.25 mm drill, from the RPi reference footprint). Please tent
  or plug them from the bottom so solder does not wick away.
* **J6/J7** (1×12 2.54 mm headers): insert from the **bottom** side, solder on top.
* **U7 ESP32-C6-MINI-1**: LGA-style module. Use the stencil aperture as in the paste layer and keep
  the antenna end clear.
* Rotations in the CPL follow KiCad's library zero orientation. Please verify the orientation of polarized parts
  (U2, U3, U4, U5, U6, U7, D1–D3, Y1, L1, J1–J5) against the assembly drawing during DFM.
* Silkscreen reference designators are hidden. Use the assembly PDFs.

## Verification status

| Check | Result |
|---|---|
| ERC (`kicad-cli sch erc`) | **0 errors, 0 warnings** (`fab/erc-report.txt`) |
| DRC (`kicad-cli pcb drc --schematic-parity`, zones refilled) | **0 errors, 0 unconnected pads, 0 schematic-parity issues**, 3 warnings (`fab/drc-report.txt`) |
| Netlist vs. source | `scripts/check_netlist.py`: KiCad netlist matches `design.py` (89 symbols, every net) |

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
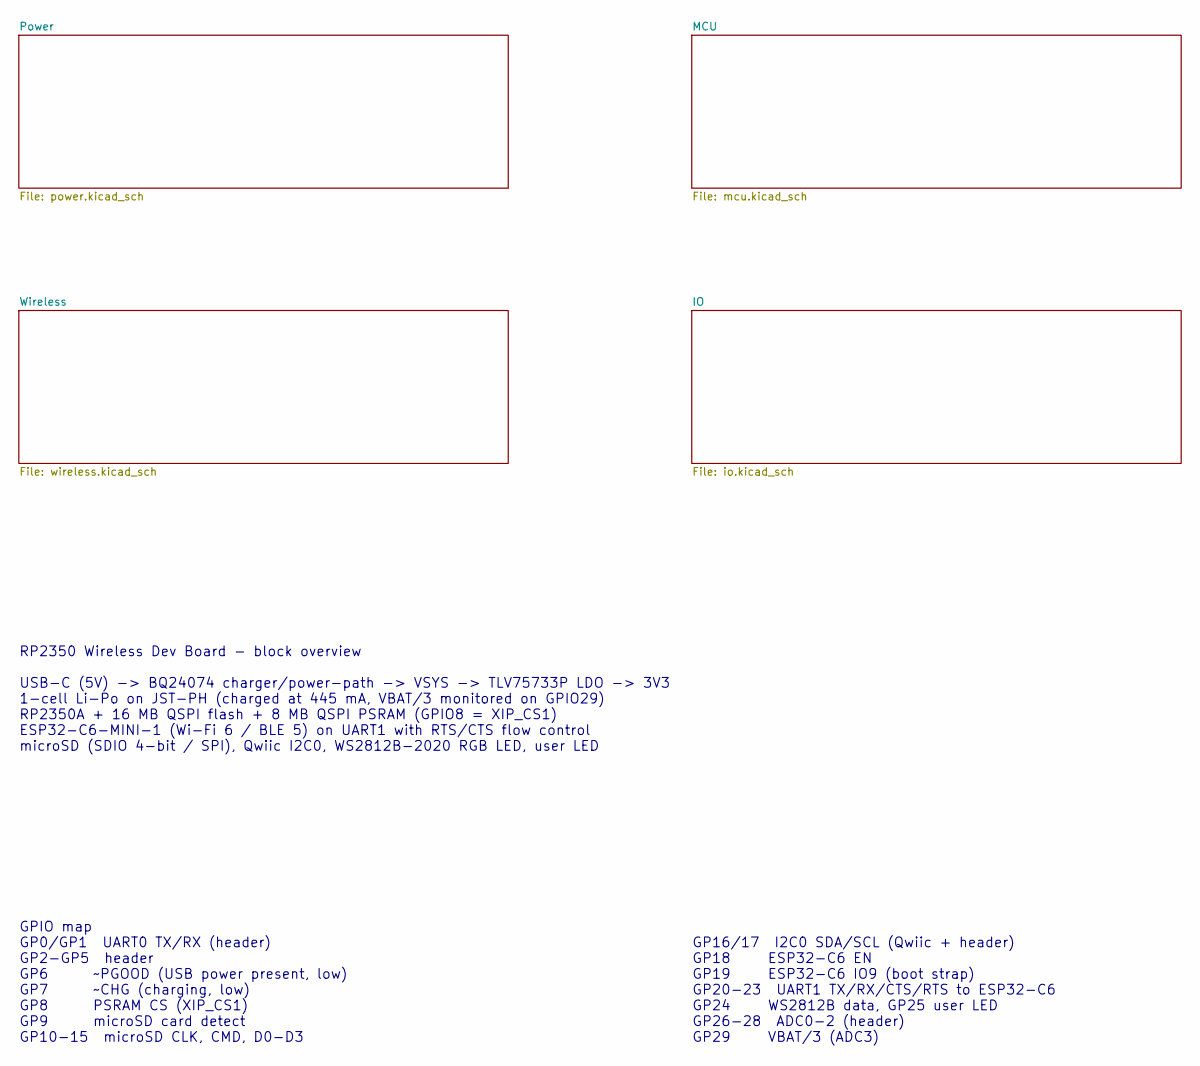
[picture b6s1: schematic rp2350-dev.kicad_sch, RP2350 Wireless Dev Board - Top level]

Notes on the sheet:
RP2350 Wireless Dev Board - block overview USB-C (5V) -> BQ24074 charger/power-path -> VSYS -> TLV75733P LDO -> 3V3 1-cell Li-Po on JST-PH (charged at 445 mA, VBAT/3 monitored on GPIO29) RP2350A + 16 MB QSPI flash + 8 MB QSPI PSRAM (GPIO8 = XIP_CS1) ESP32-C6-MINI-1 (Wi-Fi 6 / BLE 5) on UART1 with R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
GPIO map GP0/GP1 UART0 TX/RX (header) GP2-GP5 header GP6 ~PGOOD (USB power present, low) GP7 ~CHG (charging, low) GP8 PSRAM CS (XIP_CS1) GP9 microSD card detect GP10-15 microSD CLK, CMD, D0-D3
GP16/17 I2C0 SDA/SCL (Qwiic + header) GP18 ESP32-C6 EN GP19 ESP32-C6 IO9 (boot strap) GP20-23 UART1 TX/RX/CTS/RTS to ESP32-C6 GP24 WS2812B data, GP25 user LED GP26-28 ADC0-2 (header) GP29 VBAT/3 (ADC3)

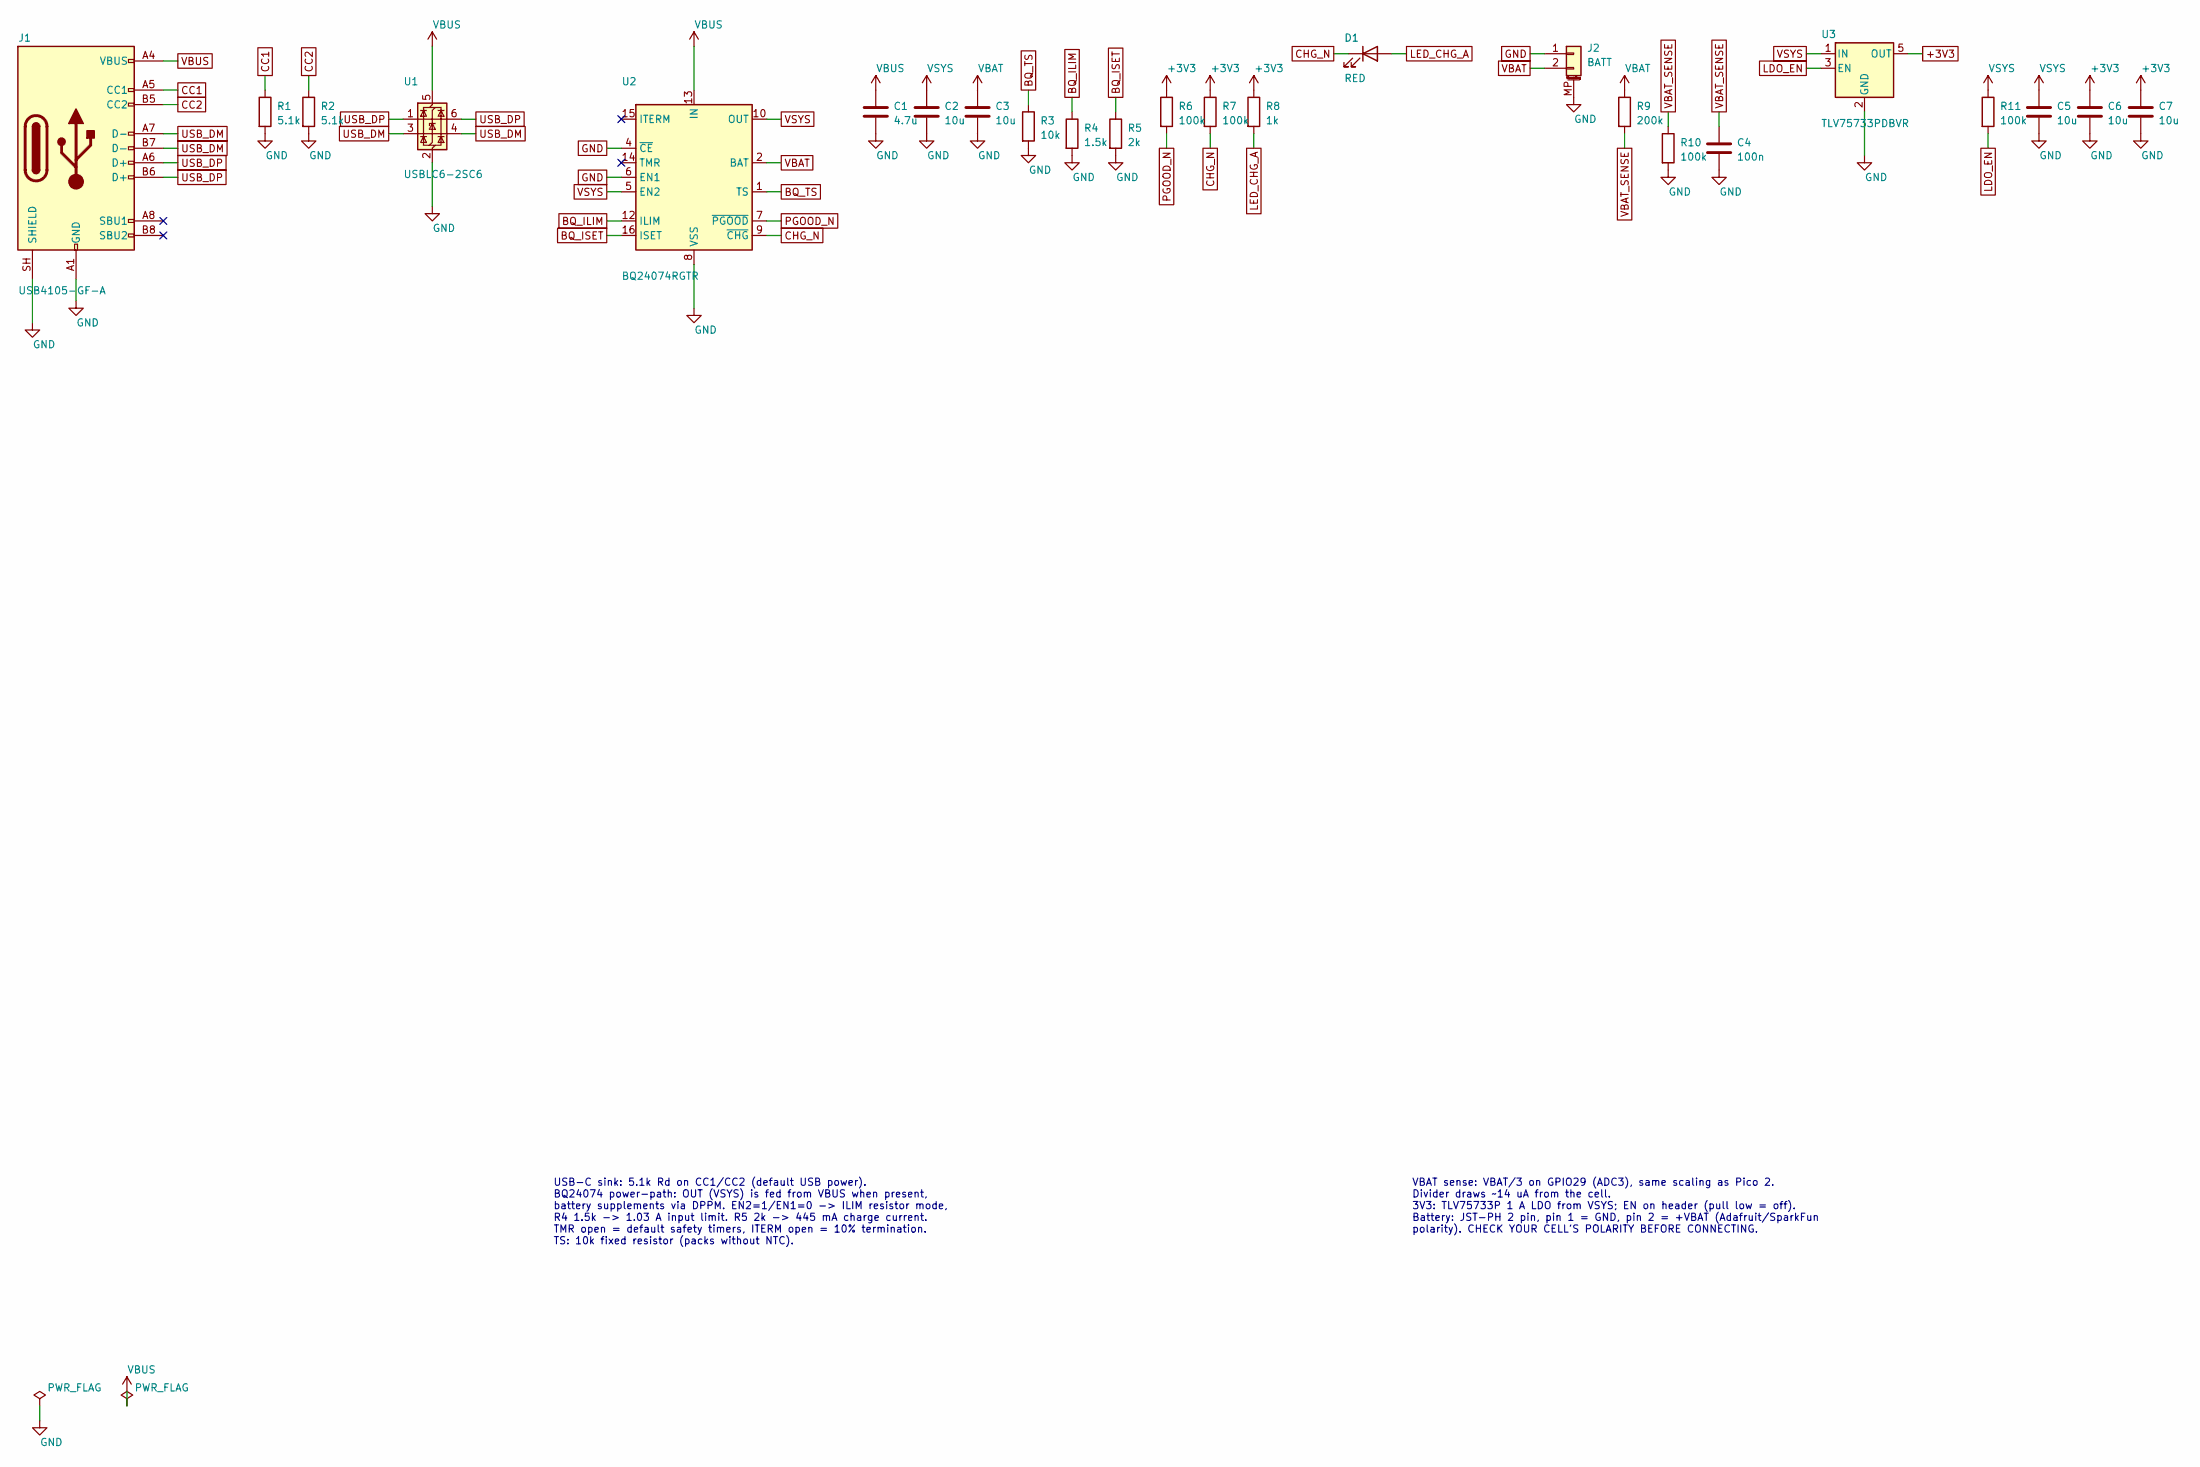
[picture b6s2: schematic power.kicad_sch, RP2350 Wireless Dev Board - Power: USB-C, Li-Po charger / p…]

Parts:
C1: 4.7u; C_0603_1608Metric; MPN CL10A475KA8NQNC; LCSC C69335
C2, C3, C5, C6, C7: 10u; C_0603_1608Metric; MPN CL10A106MA8NRNC; LCSC C96446
C4: 100n; C_0402_1005Metric; MPN CL05B104KO5NNNC; LCSC C1525
D1: RED; LED_0603_1608Metric; MPN KT-0603R; LCSC C2286
J1: USB4105-GF-A; USB_C_Receptacle_GCT_USB4105-xx-A_16P_TopMnt_Horizontal; MPN USB4105-GF-A; LCSC C3020560
J2: BATT; JST_PH_S2B-PH-SM4-TB_1x02-1MP_P2.00mm_Horizontal; MPN S2B-PH-SM4-TB(LF)(SN); LCSC C295747
R1, R2: 5.1k; R_0402_1005Metric; MPN 0402WGF5101TCE; LCSC C25905
R3: 10k; R_0402_1005Metric; MPN 0402WGF1002TCE; LCSC C25744
R4: 1.5k; R_0402_1005Metric; MPN 0402WGF1501TCE; LCSC C25867
R5: 2k; R_0402_1005Metric; MPN 0402WGF2001TCE; LCSC C4109
R6, R7, R10, R11: 100k; R_0402_1005Metric; MPN 0402WGF1003TCE; LCSC C25741
R8: 1k; R_0402_1005Metric; MPN 0402WGF1001TCE; LCSC C11702
R9: 200k; R_0402_1005Metric; MPN 0402WGF2003TCE; LCSC C25764
U1: USBLC6-2SC6; SOT-23-6; MPN USBLC6-2SC6; LCSC C7519
U2: BQ24074RGTR; VQFN-16-1EP_3x3mm_P0.5mm_EP1.6x1.6mm; MPN BQ24074RGTR; LCSC C54313
U3: TLV75733PDBVR; SOT-23-5; MPN TLV75733PDBVR; LCSC C485517

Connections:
+3V3: C6.1, C7.1, R6.1, R7.1, R8.1, U3.5 (OUT); also elsewhere on the board
BQ_ILIM: R4.1, U2.12 (ILIM)
BQ_ISET: R5.1, U2.16 (ISET)
BQ_TS: R3.1, U2.1 (TS)
CC1: J1.A5 (CC1), R1.1
CC2: J1.B5 (CC2), R2.1
CHG_N: D1.1 (K), R7.2, U2.9 (~CHG); also elsewhere on the board
GND: C1.2, C2.2, C3.2, C4.2, C5.2, C6.2, C7.2, J1.A1 (GND), J1.A12 (GND), J1.B1 (GND), J1.B12 (GND), J1.SH (SHIELD), J2.1, J2.MP (MountPin), R1.2, R2.2, R3.2, R4.2, R5.2, R10.2, U1.2 (GND), U2.4 (~CE), U2.6 (EN1), U2.8 (VSS), U2.17 (VSS), U3.2 (GND); also elsewhere on the board
LDO_EN: R11.2, U3.3 (EN); also elsewhere on the board
LED_CHG_A: D1.2 (A), R8.2
PGOOD_N: R6.2, U2.7 (~PGOOD); also elsewhere on the board
USB_DM: J1.A7 (D-), J1.B7 (D-), U1.3 (I/O2), U1.4 (I/O2); also elsewhere on the board
USB_DP: J1.A6 (D+), J1.B6 (D+), U1.1 (I/O1), U1.6 (I/O1); also elsewhere on the board
VBAT: C3.1, J2.2, R9.1, U2.2 (BAT), U2.3 (BAT); also elsewhere on the board
VBAT_SENSE: C4.1, R9.2, R10.1; also elsewhere on the board
VBUS: C1.1, J1.A4 (VBUS), J1.A9 (VBUS), J1.B4 (VBUS), J1.B9 (VBUS), U1.5 (VBUS), U2.13 (IN); also elsewhere on the board
VSYS: C2.1, C5.1, R11.1, U2.5 (EN2), U2.10 (OUT), U2.11 (OUT), U3.1 (IN); also elsewhere on the board

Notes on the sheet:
USB-C sink: 5.1k Rd on CC1/CC2 (default USB power). BQ24074 power-path: OUT (VSYS) is fed from VBUS when present, battery supplements via DPPM. EN2=1/EN1=0 -> ILIM resistor mode, R4 1.5k -> 1.03 A input limit. R5 2k -> 445 mA charge current. TMR open = default safety timers, ITERM open = 10% termin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
VBAT sense: VBAT/3 on GPIO29 (ADC3), same scaling as Pico 2. Divider draws ~14 uA from the cell. 3V3: TLV75733P 1 A LDO from VSYS; EN on header (pull low = off). Battery: JST-PH 2 pin, pin 1 = GND, pin 2 = +VBAT (Adafruit/SparkFun polarity). CHECK YOUR CELL'S POLARITY BEFORE CONNECTING.
